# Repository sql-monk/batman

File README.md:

# batman — менеджер двох акумуляторів (LiFePO₄ 8S + свинець 24 В)

Пристрій, що заряджає два акумулятори по черзі від одного DPS5015, віддає їх на спільне навантаження через ідеальні діоди з керованими ключами, і рахує, скільки кожен акумулятор прийняв і віддав.

Основа — наявні модулі з [docs/components.md](docs/components.md). Чотири однобічні плати ЛУТ: A з ESP і двома портами I²C для ADS, B з аналоговими входами та фільтрами без I²C, C з розподілом 3,3 В, D з розподілом 5 В. Два окремі ADS1115 одержують аналог із B, живлення/I²C із A. Потрібен ще один ADS1115; C/D розподіляють готове живлення, а не замінюють стабілізатори.

| Тека | Вміст |
|---|---|
| [docs/concept.md](docs/concept.md) | задум, архітектура, вибір модулів, вимірювання й підрахунок А·год, припущення, відкриті питання |
| [docs/plan.md](docs/plan.md) | план робіт: документація, схема й плати, корпус, прошивка, сервіс; порядок і критерії готовності |
| [docs/components.md](docs/components.md) | кожен модуль і базовий компонент: характеристики, розпіновка, розміри з позначкою джерела, кількість, публічні посилання |
| [docs/README.md](docs/README.md) | зміст документації, правило «одне число — одне місце», позначення |
| [docs/connections.md](docs/connections.md) | вузли, кола з номерами, GPIO ESP32, роз'єми A–D, шкала АЦП |
| [docs/dps5015-modbus.md](docs/dps5015-modbus.md) | порт, регістри, послідовності команд, помилки DPS5015 |
| [docs/measurement.md](docs/measurement.md) | вибірка, інтегрування, автонуль, SoC, NVS |
| [docs/protocol.md](docs/protocol.md) | пристрій ↔ сервіс: пошук, JSON, REST |
| [docs/firmware.md](docs/firmware.md) | вимоги до прошивки: старт, стейт-машина, параметри |
| [docs/service.md](docs/service.md) | вимоги до сервісу: БД, агрегати, сторінки, розгортання |
| [docs/enclosure/requirements.md](docs/enclosure/requirements.md) | що вмістити, зони, зазори, тепло, друк, перелік STL |
| [docs/tests.md](docs/tests.md) | бланки перевірок і результати |
| [hardware/README.md](hardware/README.md) | єдиний проєкт KiCad 10, сім сторінок схеми, розведені A–D, PDF ЛУТ, свердління, BOM, кабелі та умови допуску прототипу |
| `firmware/` | код ESP32: вимірювання, підрахунок А·год, Modbus до DPS5015, ключі, Wi-Fi-телеметрія |
| `service/` | кросплатформений сервіс (Windows → Raspberry Pi 4): пошук пристрою, збір, зберігання, агрегати, графіки |
| `mechanical/` | модель корпусу, STL, звіти придатності до друку |

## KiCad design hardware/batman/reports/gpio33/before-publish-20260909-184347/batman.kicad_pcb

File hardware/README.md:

# BATMAN: чотири модульні PCB

**CAD-прототип, не перевірений на стенді.** Основний проєкт: [batman/batman.kicad_pro](batman/batman.kicad_pro), KiCad 10.0.6+. У [спільній PCB](batman/batman.kicad_pcb) чотири замкнені контури: це чотири фізичні плати, не одна плата з міддю між ними. Схема має кореневий і шість функціональних аркушів.

## Склад

Актуальна ревізія трасування 2026-09-09: **223 сегменти (A: 85, B: 77, C: 28, D: 33), тільки напрямки 0/45/90°**. Попередня версія зі 165 сегментами довільного напрямку замінена. Компоненти, їхні кути, контакти та чотири перемички залишені на місцях; глобальний мінімум кількості перемичок не доведений. GND з'єднує заливка. Вільні кінці трас точно збігаються з центрами контактів, інші стики мають спільні центральні лінії; сегментів коротше 1 мм немає. DRC усіх плат, паритет схеми та PDF 1:1 перевірені. Експорт відхиляє некратні 45° напрямки. Опис перенесення GPIO33 нижче стосується попереднього етапу розміщення.

| PCB | Функція | Розмір, мм | Локальні перемички | Отвори |
|---|---|---|---|---|
| A | ESP32 DevKitC, два порти ADS I²C, OLED, UART DPS, SPI, кнопка, 1-Wire, драйвери реле | 78 × 78 | WA1–WA4 | 86 |
| B | Шість аналогових входів, дільники, RC-фільтри; аналогові виходи до окремих ADS | 86 × 68 | немає | 39 |
| C | Розподіл 3,3 В і кероване живлення mACS через Q3 | 43 × 33 | немає | 18 |
| D | Розподіл 5 В, діодне «АБО» B1/B2 перед зовнішнім LM2596, зірка живлення реле | 63 × 40 | немає | 32 |

Чотири перемички WA1–WA4 на A паяються до наявних контактів; B/C/D без перемичок. WA1 (+3V3) закінчується на SMD-паді R16.2, WA4 (SCL) на R17.1: ізолювати та механічно розвантажити дроти. WA2 з'єднує кнопку J11.2 з J1.7; WA3 — SCL J20.3 з J10.2. Жодна локальна перемичка не підключається до J22. Разом 175 отворів, включно з 16 монтажними M3 Ø3,4 мм. ADS1115 J2/J13 — два зовнішні модулі, посадок під них на A–D немає.

Ревізія GPIO33 2026-09-09: 352 сегменти, усі довжиною не менше 1 мм. **SENS_PWR перенесений на J1.8 / GPIO33; J1.12 / GPIO14 тепер NC.** J22 піднятий і повернутий вертикально; усі три його контакти (+3V3, GND, SENS_PWR) з'єднані з ESP міддю без локальних перемичок. Це перевірено на копії PCB без моделей дротів. Для проходу живлення пересунутий роз'єм кнопки J11. Кабель CB2 до окремої плати C залишається потрібним. У прошивці задати SENS_PWR=33, HIGH/Hi-Z=OFF, LOW=ON; старе призначення GPIO14 непридатне. Загальна площа плат зменшена приблизно на 6%. Збережені ручні позиції J6/J7/J26/R13/R18; попередні зміни J20/J21/R16/R17, C3/C4 та роз'ємів D залишені. Старі монтажні таблиці й перемички не використовувати.

Силові 10 А батарей і навантаження не проходять через ці PCB. Зовнішні модулі, запобіжники й панельні клеми залишаються у схемі. C1/C2 навісно на зовнішній шині LOAD+/GND; D3 DNP. Нова PCB B є **аналоговою**, не колишньою платою буфера.

## Міжплатні Кабелі

Порядок у таблиці: від контакту 1 до N. Кабелі однойменні, 1→1; **не перевертати за фізичним напрямком гребінки**. Звіряти номери на монтажних PDF.

| Кабель | Звідки → куди | Контакти 1…N |
|---|---|---|
| CB2 | A.J22 → C.J23 | +3V3, GND, SENS_PWR |
| CB3 | C.J24 → B.J25 | GND, +3V3_SENS |
| CB4 | D.J27 → A.J26 | +5V, GND |
| CB5 | A.J28 → D.J29 | RELAY_IN1, RELAY_IN2, GND |
| CB6 | D.X6 → B.X8 | B1, B2, GND; напруга батарей до дільників, не рівні 3,3 В |

Між A–D п'ять кабелів, 13 жил. **CB1 вилучений; J21 тепер на A. Старі кабелі J20/J21 і J24/J25 несумісні з цією ревізією.** [interboard-cables.csv](batman/output/interboard-cables.csv) містить кожну жилу CB2–CB6. `WC*` на спільній PCB моделюють зовнішні дроти, не мідь. Лінії Dwgs.User показують відповідність кінців, не маршрут і довжину джгута.

## Підключення Окремих ADS

| Роз'єм PCB | Контакти PCB 1…N | Зовнішній модуль і контакти |
|---|---|---|
| A.J20 | +3V3, GND, SCL, SDA | J2 (0x48): VDD, GND, SCL, SDA |
| A.J21 | +3V3, GND, SCL, SDA | J13 (0x49): VDD, GND, SCL, SDA |
| B.J32 | I_B1, I_B2, U_B1, U_B2, GND | J2: A0, A1, A2, A3, GND |
| B.J33 | I_LOAD, U_LOAD, GND | J13: A0, A1, GND |

Це ще чотири кабелі, 16 жил, не включені в CB2–CB6. Точні контакти — [cable-map.csv](batman/output/cable-map.csv). На кожному ADS обидві землі кабелів з'єднати в локальній точці GND із надійною ізоляцією та розвантаженням дротів; один контакт модуля не означає два незалежні гнізда.

J20/J21 — два роз'єми **однієї** шини GPIO22=SCL/GPIO21=SDA. Є одна пара R16/R17 по 4,7 кОм до 3V3 на A; не додавати ще одну пару для другого порту. C6/C10 — локальні 100 нФ VDD–GND біля відповідного зовнішнього ADS, не на B: перевірити наявність на модулі, за відсутності встановити. Перемички ADDR та невикористані входи — [ads-configuration.csv](batman/output/ads-configuration.csv).

I²C: початково 100 кГц, короткий внутрішній кабель до 20 см, подалі від силових дротів. Перевірити фронти осцилографом і сумарні підтяжки на A, ADS-модулях та OLED: врахувати паралельний опір і допустимий струм LOW. Це не інтерфейс для довгого зовнішнього кабелю. CB6 вести окремо від I²C; дроти B1/B2 мають бути захищені від КЗ біля джерела.

## Аналогова Плата B І Канали

На B немає ADS, SDA/SCL і неперемиканої шини +3V3. Потрібні **два окремі модулі ADS1115**, один додатковий до початкового комплекту. Їхні позначення J2/J13 збережені у схемі, але мають власника EXTERNAL. Перевірити маркування `VDD GND SCL SDA ADDR ALRT A0 A1 A2 A3`. Локально на J2 ADDR з'єднати з GND, на J13 з VDD; спочатку розімкнути заводську перемичку ADDR→GND другого модуля, інакше буде КЗ. На J13 локально заземлити A2/A3, обидва ALRT залишити NC.

| АЦП | Адреса | A0 | A1 | A2 | A3 |
|---|---|---|---|---|---|
| J2 | 0x48 | I_B1 | I_B2 | U_B1 | U_B2 |
| J13 | 0x49 | I_LOAD | U_LOAD | GND | GND |

Обидва PGA ±4,096 В, 475 SPS; це діапазон перетворення, **не дозвіл перевищувати живлення на вході**. Дільники: U_B1/U_B2 100k/10k, U_LOAD 100k/4,7k. Струми через RC 1k/1u; напруги через дільники й 100n. GPIO34/39 ESP тепер NC, аналогових кабелів до A немає. ALRT не підключені, готовність опитувати через I²C.

ADS розмістити біля B; аналогові кабелі початково до 10 см, окремо від силових і цифрових джгутів. Перевірити шум та зміщення при передачі Wi-Fi й роботі реле. Усі підключення робити з вимкненим живленням: напруга на B1/B2/LOAD може підживлювати знеструмлений ADS через входи. Живі аналогові входи без живлення ADC не допускаються; схема не містить окремого захисту від такого режиму.

mACS мають лише VCC/GND/VOUT, без FAULT. J3/J4: VOUT, GND, VCC; J5: VCC, VOUT, GND. Збережене припущення ACS711EX 3,3 В / 90 мВ/А. Позначення власника `VSS` неоднозначне: **не подавати плюс без перевірки моделі та маркування**. Датчик на 5 В не є прямою заміною.

## Живлення

**C і D є розподільними платами, не новими стабілізаторами.**

- D.X1: B1, B2, GND. P28 від зовнішньої мінус-шини до D.X1.3. VD1/VD2 формують VIN_DC на D.X2.1 для входу наявного LM2596; X2.2 GND. Його вихід, заздалегідь виставлений на 5,0 В, підключається до D.X3.1/2.
- D.J27 живить VIN DevKitC на A через CB4. D.J31: резервний вихід 5V/GND, штатно без навантаження. 5 В потрібні DevKitC і реле.
- D.J8: IN1, GND, IN2, VCC, JD-VCC. Перемичку VCC–JD-VCC на реле зняти. NT1 біля X3 є мідною зіркою; гілки опто та котушок не об'єднувати біля J8.
- 3,3 В утворює стабілізатор DevKitC. A.J20/J21 живлять окремі ADS, A.J22 передає 3V3 на C.J23. C.J24 живить тільки датчики через B; Q3 комутує +3V3_SENS. SENS_PWR LOW=ON, HIGH/Hi-Z=OFF. C.J30: резервний 3V3/GND, штатно без навантаження.
- **Не підключати зовнішнє джерело до A.J20/J21 або C.J30:** це виходи 3V3 DevKitC. C.J24 також не є входом живлення. USB одночасно із зовнішнім VIN дозволений лише після перевірки конкретного DevKitC на зворотне підживлення.

Орієнтовна початкова межа зовнішнього навантаження 3,3 В: до 100 мА сумарно на ADS, mACS, OLED, підтяжки й периферію, **лише якщо конкретний DevKitC має такий запас після власного споживання**. Це не паспортний рейтинг плати. Піки Wi-Fi, котушки, нагрів LDO, падіння на Q3 й кабелях перевірити на стенді. Резервні виходи не створюють додаткової потужності. За браку запасу потрібна інша ревізія з окремим стабілізатором 3,3 В, не паралельне підключення джерел.

GND спільний. Через CB2–CB6, цифрові й аналогові кабелі ADS та UART є кілька шляхів повернення струму: модульність **не забезпечує гальванічної розв'язки чи відсутності петель землі**. Силові повернення вести окремо, перевірити топологію на стенді.

## Виготовлення

ЛУТ, тільки **B.Cu**: сигнали ≥0,8 мм; GND і живлення 3,3/5 В ≥1,0 мм; B1/B2/LOAD+/VIN_DC ≥1,2 мм. Зазор за участю доріжки ≥0,65 мм, між готовими падами ≥0,5 мм; від батарейних мереж B1/B2/LOAD+/VIN_DC до іншої міді ≥1,0 мм, включно із заливкою. Відступ від краю ≥0,5 мм. Це технологічний запас для низьковольтного батарейного пристрою, не сертифікація ізоляції та не дозвіл підвищувати робочу напругу або струм. Силові 10 А залишаються поза PCB.

Без via, mask/paste. THT-пади номінально мають F.Cu у KiCad, але цей шар не виготовляється. Резистори лише 1206; C3–C5, C7–C9, C11–C13 мають альтернативні THT/1206-пади, ставити **один** корпус на позицію. C1/C2 зовнішні на шині, C6/C10 біля зовнішніх ADS.

| Плата | Мідь, дзеркало 1:1 | Монтаж |
|---|---|---|
| A | [A/copper-mirrored.pdf](batman/output/A/copper-mirrored.pdf) | [A/assembly.pdf](batman/output/A/assembly.pdf) |
| B | [B/copper-mirrored.pdf](batman/output/B/copper-mirrored.pdf) | [B/assembly.pdf](batman/output/B/assembly.pdf) |
| C | [C/copper-mirrored.pdf](batman/output/C/copper-mirrored.pdf) | [C/assembly.pdf](batman/output/C/assembly.pdf) |
| D | [D/copper-mirrored.pdf](batman/output/D/copper-mirrored.pdf) | [D/assembly.pdf](batman/output/D/assembly.pdf) |

У кожній теці A–D є недзеркальна мідь, wiring.pdf, Excellon/карта свердління й Gerber. Спільні PDF у output показують усі чотири плати, не стару 100×80 PCB. Друк Actual size / 100%, без Fit; перевірити лінійкою контур і крок 2,54 мм.

[pinout.csv](batman/output/pinout.csv): контакти від лівого верхнього кута своєї PCB. [drill-list.csv](batman/output/drill-list.csv) і [drill-summary.csv](batman/output/drill-summary.csv): отвори за платами. [jumpers.csv](batman/output/jumpers.csv): WA1–WA4 на A. [cable-map.csv](batman/output/cable-map.csv): кабелі зовнішніх модулів, включно з ADS. [bom.csv](batman/output/bom.csv): J1 — DevKitC із гніздами, J2/J13 — окремі ADS, не дублікати модулів.

## Перевірки Та Обмеження

ERC, DRC/паритет спільної PCB, DRC кожної локальної плати та PDF 1:1: [validation.json](batman/reports/validation.json), [pdf-validation.json](batman/reports/pdf-validation.json). Експорт перевіряє відсутність міжплатної міді, сегментів коротше 1 мм та правильні контакти кабелів ADS. Для роботи потрібні чотири перемички A, п'ять кабелів CB2–CB6, чотири кабелі до ADS і їхні локальні з'єднання ADDR/A2/A3/GND. DRC не перевіряє фактичний зовнішній монтаж.

До виготовлення звірити посадки DevKitC (38 пінів, міжряддя 25,4 мм), клемників 5,00 мм, BC547/BC557 C-B-E та осьових 1N5819 K-A. MCU: USB унизу, антена зверху; keepout на A не замінює перевірки реального модуля. Зовнішні ADS закріпити на ізольованих тримачах біля B, не залишати на дротах. **Корпуси та висоти не обміряні; DRC не перевіряє їхню посадку.** Джгути не прокладати над антеною.

До підключення батарей закрити попередні питання безпеки: реле 10 А проти старої вимоги прошивки 12 А; відсутність апаратного взаємоблокування K1/K2; неможливість гарантувати безструмову комутацію при всіх відмовах DPS; ground-loop через UART. D3 DNP: напис 33 В не гарантує обмеження до 35 В. Не перевищувати 10 А на наявному реле. FAULT від mACS немає. Перший запуск з обмеженням струму, без батарей і силового навантаження. Стендові випробування не виконані.

## Відтворення

Наведений нижче старий процес **не відтворює актуальні 223 сегменти**. Поточний результат збережений у головній PCB та reports/routing45/staged. [octilinear.py](octilinear.py) обмежує маршрути напрямками 0/45/90°; [clean_paths.py](clean_paths.py) без цього обмеження дозволяє довільні кути й не відтворює поточну ревізію. Інструменти в reports/routing45 використовують історичні знімки, а не нові ручні правки. Локальні плати мають світові координати основної збірки: старий `modular.py --merge` повторно змістить їх. Для актуального комплекту не запускати старі `--finish-copper`, `polish.py` або `--merge`; перевірка та експорт головної PCB через `export.py` підтримуються.

[circuit.py](circuit.py): з'єднання й власники деталей; [connector_pinout.json](connector_pinout.json): зовнішні роз'єми; [modular-layout.json](modular-layout.json): геометрія; [modular.py](modular.py): плати й кабелі. Старі floorplan.json / placement.py / placement.json не керують цією ревізією. Прямі одноплатні входи pcb.py і freeroute.py вимкнені.

```powershell
$python = "$env:LOCALAPPDATA\Programs\KiCad\10.0\bin\python.exe"
& $python hardware/circuit.py
& $python hardware/modular.py --route --finish-copper --wire
foreach ($board in @('A', 'B', 'C', 'D')) {
	& $python hardware/polish.py "hardware/batman/reports/$board/candidate.kicad_pcb"
	if ($LASTEXITCODE -ne 0) { throw "PCB $board needs local correction" }
}
& $python hardware/modular.py --merge
& "$env:LOCALAPPDATA\Programs\KiCad\10.0\bin\kicad-cli.exe" pcb drc --refill-zones --save-board --exit-code-violations hardware/batman/batman.kicad_pcb
& $python hardware/export.py
python hardware/review_pdf.py
```

Потрібні pcbnew/numpy/sexpdata у Python KiCad, Java 25 і Freerouting 2.4.1 (`FREEROUTING_JAVA`, `FREEROUTING_JAR`, або перевірені файли в TEMP); PyMuPDF потрібний лише останній перевірці. Трасування локальне, API/аналітика вимкнені. `--board A` (або B/C/D) обмежує трасування однією платою; `--merge` збирає всі чотири. Не використовувати старі SES після зміни контактів чи геометрії.

Генератори **перезаписують** CAD. Не запускати поверх ручних правок без перенесення їх у модель. Технічні знімки й настройки DRC у reports/A–D, відкривати для роботи основний batman.kicad_pro. [batman.kicad_dru](batman/batman.kicad_dru) переносити разом із проєктом. Після зовнішньої перебудови не зберігати старий відкритий у KiCad вміст поверх нового.

[polish.py](polish.py) є історичним інструментом видалення та злиття коротких сегментів; подовження окремих шматків прибране. Чистий DRC сам по собі не гарантує акуратних стиків центральних ліній. [refine.py](refine.py) зберігає історичний експеримент у reports/refinement, використовує зафіксований saved-input і не є входом для імпорту майбутніх ручних правок.

[gpio33.py](gpio33.py) зберігає кандидат перенесення GPIO33 у reports/gpio33. `--check-j22` вилучає моделі перемичок тільки з тестової копії та перевіряє мідну зв'язність J22 з J1 по всіх трьох мережах. Очікувані обриви інших мереж у copper-only-drc.json не є DRC виробничої PCB. Скрипт використовує свій зафіксований saved-input; для майбутніх ручних правок цей знімок не є актуальним джерелом.

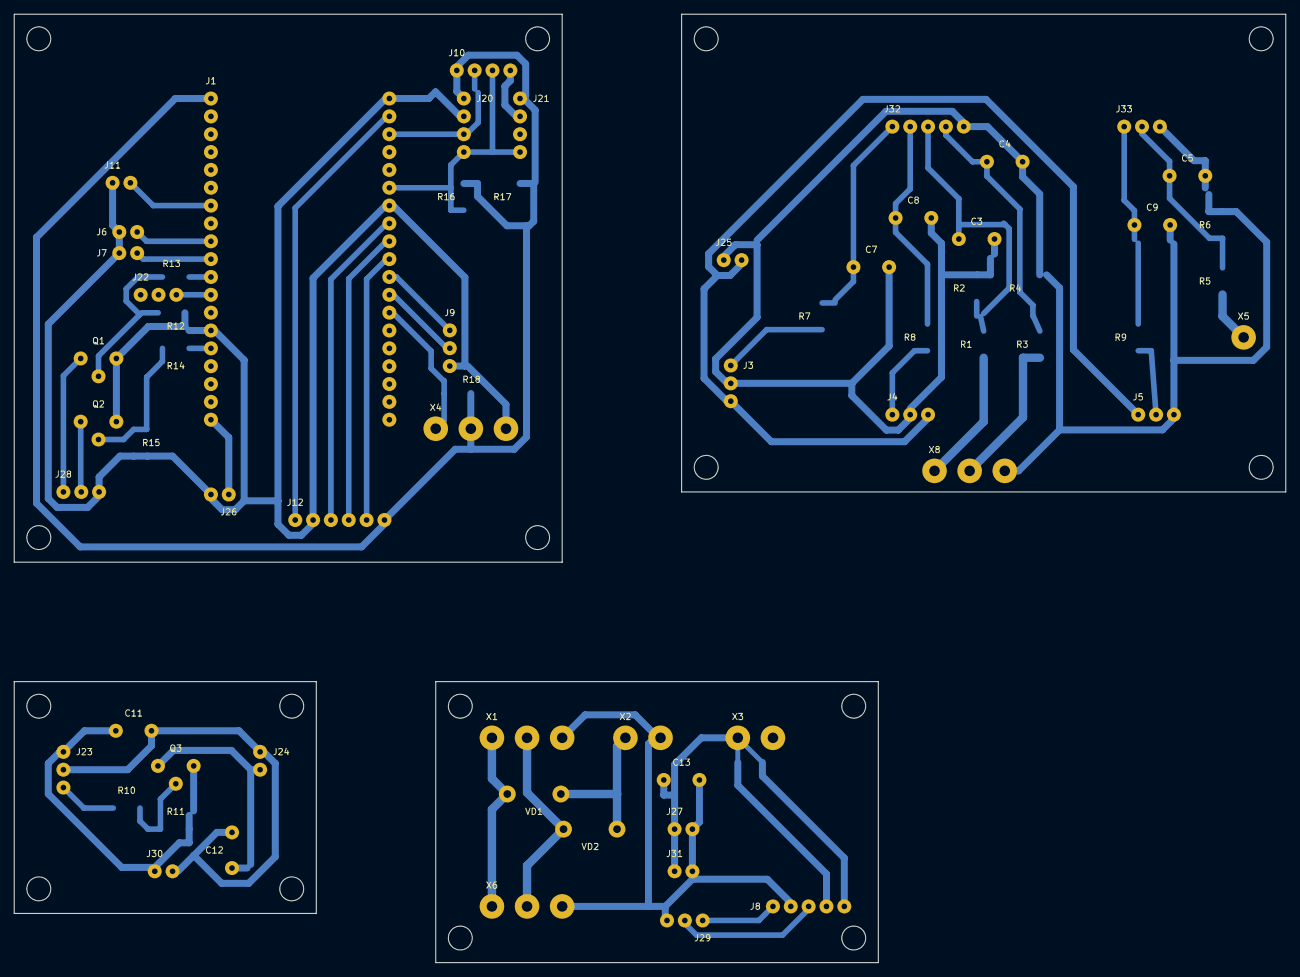
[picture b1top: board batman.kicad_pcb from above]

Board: 2 copper layers, 181.0 x 135.0 mm, 99 parts (0 on the bottom side), 39 nets.

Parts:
C3: 100n_50V; LUT_C3
C4: 100n_50V; LUT_C4
C5: 100n_50V; LUT_C5
C7: 1u_16V; LUT_C7
C8: 1u_16V; LUT_C8
C9: 1u_16V; LUT_C9
C11: 100n_16V; LUT_C11
C12: 100n_16V; LUT_C12
C13: 100n_16V; LUT_C13
HA1, HA2, HA3, HA4: M3_NPTH_3.4; Mount_M3
HB1, HB2, HB3, HB4: M3_NPTH_3.4; Mount_M3
HC1, HC2, HC3, HC4: M3_NPTH_3.4; Mount_M3
HD1, HD2, HD3, HD4: M3_NPTH_3.4; Mount_M3
J1: DevKitC_38_socket_mMCU; LUT_J1
J3: ACS1_3WIRE; LUT_J3
J4: ACS2_3WIRE; LUT_J4
J5: ACS3_3WIRE; LUT_J5
J6: SW1_GND_ON; LUT_J6
J7: SW2_GND_ON; LUT_J7
J8: RELAY; LUT_J8
J9: DPS_UART; LUT_J9
J10: OLED_I2C; LUT_J10
J11: BUTTON; LUT_J11
J12: SPI; LUT_J12
J20: LINK_+3V3_GND_SCL_SDA; LUT_J20
J21: LINK_+3V3_GND_SCL_SDA; LUT_J21
J22: LINK_+3V3_GND_SENS_PWR; LUT_J22
J23: LINK_+3V3_GND_SENS_PWR; LUT_J23
J24: LINK_GND_+3V3_SENS; LUT_J24
J25: LINK_GND_+3V3_SENS; LUT_J25
J26: LINK_+5V_GND; LUT_J26
J27: LINK_+5V_GND; LUT_J27
J28: LINK_RELAY_IN1_RELAY_IN2_GND; LUT_J28
J29: LINK_RELAY_IN1_RELAY_IN2_GND; LUT_J29
J30: LINK_+3V3_GND; LUT_J30
J31: LINK_+5V_GND; LUT_J31
J32: LINK_I_B1_I_B2_U_B1_U_B2_GND; LUT_J32
J33: LINK_I_LOAD_U_LOAD_GND; LUT_J33
NT1: COPPER_STAR_AT_X3; LUT_NT1
Q1: BC547_CBE; LUT_Q1
Q2: BC547_CBE; LUT_Q2
Q3: BC557_CBE; LUT_Q3
R1: 100k_1%; LUT_R1
R2: 10k_1%; LUT_R2
R3: 100k_1%; LUT_R3
R4: 10k_1%; LUT_R4
R5: 100k_1%; LUT_R5
R6: 4.7k_1%; LUT_R6
R7: 1k; LUT_R7
R8: 1k; LUT_R8
R9: 1k; LUT_R9
R10: 4.7k; LUT_R10
R11: 10k; LUT_R11
R12: 1k; LUT_R12
R13: 10k; LUT_R13
R14: 1k; LUT_R14
R15: 10k; LUT_R15
R16: 4.7k; LUT_R16
R17: 4.7k; LUT_R17
R18: 4.7k; LUT_R18
VD1: 1N5819; LUT_VD1
VD2: 1N5819; LUT_VD2
WA1: INSULATED_WIRE; LUT_WA1
WA2: INSULATED_WIRE; LUT_WA2
WA3: INSULATED_WIRE; LUT_WA3
WA4: INSULATED_WIRE; LUT_WA4
WA5: INSULATED_WIRE; LUT_WA5
WC2_1: EXTERNAL_CABLE_NOT_PCB; LUT_WC2_1
WC2_2: EXTERNAL_CABLE_NOT_PCB; LUT_WC2_2
WC2_3: EXTERNAL_CABLE_NOT_PCB; LUT_WC2_3
WC3_1: EXTERNAL_CABLE_NOT_PCB; LUT_WC3_1
WC3_2: EXTERNAL_CABLE_NOT_PCB; LUT_WC3_2
WC4_1: EXTERNAL_CABLE_NOT_PCB; LUT_WC4_1
WC4_2: EXTERNAL_CABLE_NOT_PCB; LUT_WC4_2
WC5_1: EXTERNAL_CABLE_NOT_PCB; LUT_WC5_1
WC5_2: EXTERNAL_CABLE_NOT_PCB; LUT_WC5_2
WC5_3: EXTERNAL_CABLE_NOT_PCB; LUT_WC5_3
WC6_1: EXTERNAL_CABLE_NOT_PCB; LUT_WC6_1
WC6_2: EXTERNAL_CABLE_NOT_PCB; LUT_WC6_2
WC6_3: EXTERNAL_CABLE_NOT_PCB; LUT_WC6_3
X1: B1_B2_GND; LUT_X1
X2: VIN_DC_GND; LUT_X2
X3: 5V_GND; LUT_X3
X4: DS18B20; LUT_X4
X5: U_LOAD_SENSE; LUT_X5
X6: BAT_SENSE_TO_B; LUT_X6
X8: BAT_SENSE_FROM_D; LUT_X8

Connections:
+3V3: C11.1, J1.1, J10.1, J12.6, J20.1, J21.1, J22.1, J23.1, J30.1, Q3.3, R11.2, R16.2, R17.2, R18.2, WA1.1, WC2_1.1, X4.2
+3V3_SENS: C12.1, J3.3, J4.3, J5.1, J24.2, J25.2, Q3.1, WC3_2.1
+5V: C13.1, J1.19, J26.1, J27.1, J31.1, NT1.1, WC4_1.1, X3.1
+5V_RELAY_COIL: J8.5, NT1.3
+5V_RELAY_VCC: J8.4, NT1.2
B1: R1.1, VD1.2, WC6_1.1, X1.1, X6.1, X8.1
B2: R3.1, VD2.2, WC6_2.1, X1.2, X6.2, X8.2
BASE1: Q1.2, R12.2, R13.1
BASE2: Q2.2, R14.2, R15.1
BASE3: Q3.2, R10.2, R11.1
BTN: J1.7, J11.2
CS: J1.29, J12.5
DPS_RX: J1.31, J9.2
DPS_TX: J1.30, J9.1
GND: C3.2, C4.2, C5.2, C7.2, C8.2, C9.2, C11.2, C12.2, C13.2, J1.14, J1.20, J1.26, J3.2, J4.2, J5.3, J6.1, J7.1, J8.2, J9.3, J10.4, J11.1, J12.2, J20.2, J21.2, J22.2, J23.2, J24.1, J25.1, J26.2, J27.2, J28.3, J29.3, J30.2, J31.2, J32.5, J33.3, Q1.3, Q2.3, R2.2, R4.2, R6.2, R13.2, R15.2, WA2.1, WA3.1, WC2_2.1, WC3_1.1, WC4_2.1, WC5_3.1, WC6_3.1, X1.3, X2.2, X3.2, X4.3, X6.3, X8.3
I_B1: C7.1, J32.1, R7.2
I_B2: C8.1, J32.2, R8.2
I_LOAD: C9.1, J33.1, R9.2
I_RAW1: J3.1, R7.1
I_RAW2: J4.1, R8.1
I_RAW3: J5.2, R9.1
K1: J1.11, R12.1
K2: J1.15, R14.1
LOAD+: R5.1, X5.1
MISO: J1.27, J12.3
MOSI: J1.21, J12.1
OW: J1.32, R18.1, X4.1
RELAY_IN1: J8.1, J28.1, J29.1, Q1.1, WC5_1.1
RELAY_IN2: J8.3, J28.2, J29.2, Q2.1, WC5_2.1
SCK: J1.28, J12.4
SCL: J1.22, J10.2, J20.3, J21.3, R17.1, WA4.1, WA5.1
SDA: J1.25, J10.3, J20.4, J21.4, R16.1
SENS_PWR: J1.12, J22.3, J23.3, R10.1, WC2_3.1
SW1_ON: J1.9, J6.2
SW2_ON: J1.10, J7.2
U_B1: C3.1, J32.3, R1.2, R2.1
U_B2: C4.1, J32.4, R3.2, R4.1
U_LOAD: C5.1, J33.2, R5.2, R6.1
VIN_DC: VD1.1, VD2.1, X2.1

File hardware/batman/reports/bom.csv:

Reference,Documentation_alias,Value,Quantity,Location,Populate
J1,,DevKitC_38_socket_mMCU,1,A,yes
J2,,ADS1115_socket_mADC,1,A,yes
J3,,ACS1_3WIRE,1,A,yes
J4,,ACS2_3WIRE,1,A,yes
J5,,ACS3_3WIRE,1,A,yes
J6,,SW1_GND_ON,1,A,yes
J7,,SW2_GND_ON,1,A,yes
J8,,RELAY,1,A,yes
J9,,DPS_UART,1,A,yes
J10,,OLED_I2C,1,A,yes
J11,,BUTTON,1,A,yes
J12,,SPI,1,A,yes
X1,,B1_B2_GND,1,A,yes
X2,,VIN_DC_GND,1,A,yes
X3,,5V_GND,1,A,yes
X4,,DS18B20,1,A,yes
X5,,U_LOAD_SENSE,1,A,yes
NT1,,COPPER_STAR_AT_X3,1,A,copper only
VD1,,1N5819,1,A,yes
VD2,,1N5819,1,A,yes
R1,,100k_1%,1,A,yes
R2,,10k_1%,1,A,yes
C3,,100n_50V,1,A,yes
R3,,100k_1%,1,A,yes
R4,,10k_1%,1,A,yes
C4,,100n_50V,1,A,yes
R5,,100k_1%,1,A,yes
R6,,4.7k_1%,1,A,yes
C5,,100n_50V,1,A,yes
R7,,1k,1,A,yes
C7,,1u_16V,1,A,yes
R8,,1k,1,A,yes
C8,,1u_16V,1,A,yes
R9,,1k,1,A,yes
C9,,1u_16V,1,A,yes
C6,,100n_16V,1,A,yes
R10,,4.7k,1,A,yes
R11,,10k,1,A,yes
Q3,,BC557_CBE,1,A,yes
R12,,1k,1,A,yes
R13,,10k,1,A,yes
Q1,,BC547_CBE,1,A,yes
R14,,1k,1,A,yes
R15,,10k,1,A,yes
Q2,,BC547_CBE,1,A,yes
R16,,4.7k,1,A,yes
R17,,4.7k,1,A,yes
R18,,4.7k,1,A,yes
XLP1,XLP,LOAD_P06_P12_P13,1,external,yes
XGND1,XGND,GND_P24_P25_P26_P27_P28,1,external,yes
C1,,100u_50V_ALUMINIUM,1,external,yes
C2,,100n_50V,1,external,yes
D3,,1.5KE33A_DNP,1,external,DNP
XB1,,BAT1_PANEL,1,external,yes
F1,,ATO_15A,1,external,yes
mACS1,,ACS711EX_15.5A,1,external,yes
mSW1,,Pololu_2815_HP,1,external,yes
mDIO1,,XL74610,1,external,yes
XB2,,BAT2_PANEL,1,external,yes
F2,,ATO_15A,1,external,yes
mACS2,,ACS711EX_15.5A,1,external,yes
mSW2,,Pololu_2815_HP,1,external,yes
mDIO2,,XL74610,1,external,yes
mACS3,,ACS711EX_15.5A,1,external,yes
Fout1,Fout,ATO_15A,1,external,yes
XLOAD1,XLOAD,LOAD_PANEL,1,external,yes
XPSU1,XPSU,PSU_33V_10A_PANEL,1,external,yes
mDPS1,mDPS,DPS5015_9600_8N1_ADDR1,1,external,yes
Fchg1,Fchg,ATO_15A,1,external,yes
mDIO3,,XL74610,1,external,yes
mREL2,,FL_3FF_5V_10A_REMOVE_JUMPER,1,external,yes
mDC5,,LM2596_SET_5.0V_FIRST,1,external,yes
mOLED1,mOLED,SSD1306_0x3C,1,external,yes
T1,,DS18B20_PROBE,1,external,yes
T2,,DS18B20_PROBE,1,external,yes
SW1,,PANEL_BUTTON_NO,1,external,yes

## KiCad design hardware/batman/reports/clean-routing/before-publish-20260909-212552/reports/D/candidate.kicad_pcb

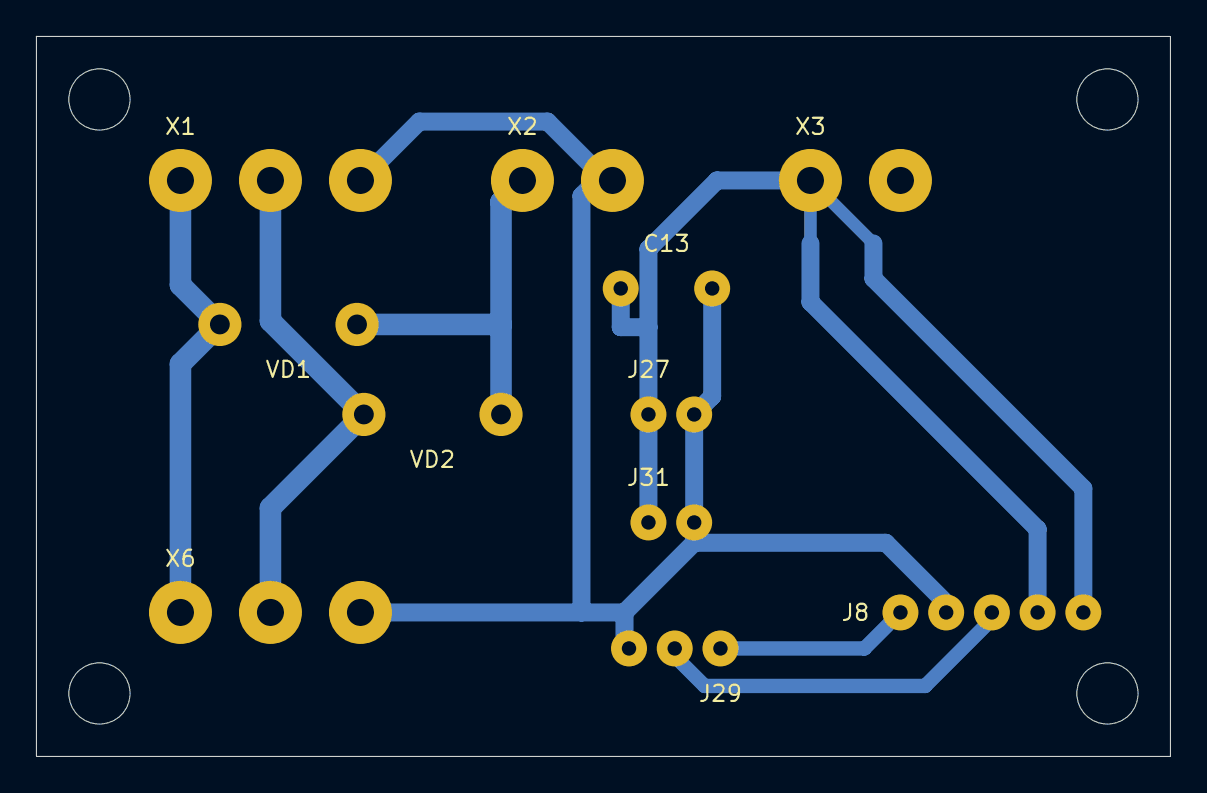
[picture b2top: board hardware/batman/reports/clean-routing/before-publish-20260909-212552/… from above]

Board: 2 copper layers, 63.0 x 40.0 mm, 16 parts (0 on the bottom side), 9 nets.

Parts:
C13: 100n_16V; LUT_C13
HD1, HD2, HD3, HD4: M3_NPTH_3.4; Mount_M3
J8: RELAY; LUT_J8
J27: LINK_+5V_GND; LUT_J27
J29: LINK_RELAY_IN1_RELAY_IN2_GND; LUT_J29
J31: LINK_+5V_GND; LUT_J31
NT1: COPPER_STAR_AT_X3; LUT_NT1
VD1: 1N5819; LUT_VD1
VD2: 1N5819; LUT_VD2
X1: B1_B2_GND; LUT_X1
X2: VIN_DC_GND; LUT_X2
X3: 5V_GND; LUT_X3
X6: BAT_SENSE_TO_B; LUT_X6

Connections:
+5V: C13.1, J27.1, J31.1, NT1.1, X3.1
+5V_RELAY_COIL: J8.5, NT1.3
+5V_RELAY_VCC: J8.4, NT1.2
B1: VD1.2, X1.1, X6.1
B2: VD2.2, X1.2, X6.2
GND: C13.2, J8.2, J27.2, J29.3, J31.2, X1.3, X2.2, X3.2, X6.3
RELAY_IN1: J8.1, J29.1
RELAY_IN2: J8.3, J29.2
VIN_DC: VD1.1, VD2.1, X2.1

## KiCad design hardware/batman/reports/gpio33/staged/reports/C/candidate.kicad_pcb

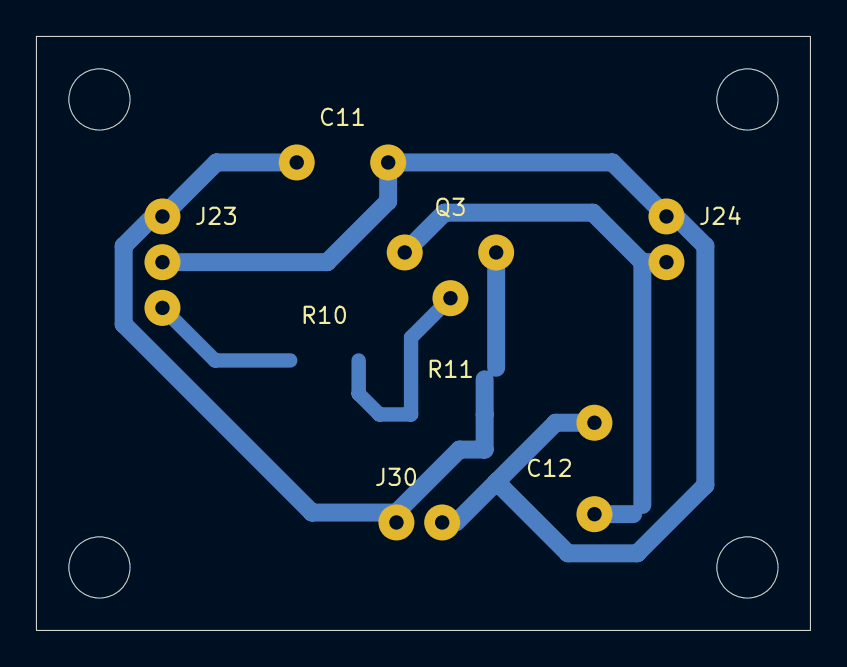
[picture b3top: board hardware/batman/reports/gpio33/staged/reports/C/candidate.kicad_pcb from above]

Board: 2 copper layers, 43.0 x 33.0 mm, 12 parts (0 on the bottom side), 5 nets.

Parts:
C11: 100n_16V; LUT_C11
C12: 100n_16V; LUT_C12
HC1, HC2, HC3, HC4: M3_NPTH_3.4; Mount_M3
J23: LINK_+3V3_GND_SENS_PWR; LUT_J23
J24: LINK_GND_+3V3_SENS; LUT_J24
J30: LINK_+3V3_GND; LUT_J30
Q3: BC557_CBE; LUT_Q3
R10: 4.7k; LUT_R10
R11: 10k; LUT_R11

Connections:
+3V3: C11.1, J23.1, J30.1, Q3.3, R11.2
+3V3_SENS: C12.1, J24.2, Q3.1
BASE3: Q3.2, R10.2, R11.1
GND: C11.2, C12.2, J23.2, J24.1, J30.2
SENS_PWR: J23.3, R10.1

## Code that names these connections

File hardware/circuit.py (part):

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    right = ["GND", "GPIO23", "GPIO22", "GPIO1", "GPIO3", "GPIO21", "GND", "GPIO19",
             "GPIO18", "GPIO5", "GPIO17", "GPIO16", "GPIO4", "GPIO0", "GPIO2",
             "GPIO15", "GPIO8", "GPIO7", "GPIO6"]
    gpio = {"3V3": "+3V3", "GND": "GND", "VIN": "+5V", "GPIO39": "I_LOAD",
            "GPIO34": "U_LOAD", "GPIO32": "BTN", "GPIO25": "SW1_ON",
            "GPIO26": "SW2_ON", "GPIO27": "K1", "GPIO33": "SENS_PWR", "GPIO13": "K2",
            "GPIO23": "MOSI", "GPIO22": "SCL", "GPIO21": "SDA", "GPIO19": "MISO",
            "GPIO18": "SCK", "GPIO5": "CS", "GPIO17": "DPS_TX", "GPIO16": "DPS_RX",
            "GPIO4": "OW"}
    pin_names = left + right
    pin_types = ["power_out" if name == "3V3" else "power_in" if name in ("GND", "VIN")
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    assert len(by_ref) == len(parts)
    pins = {name: net for _, name, net, _ in by_ref["J1"].pins}
    assert pins["GPIO39"] is None and pins["GPIO34"] is None
    assert pins["GPIO33"] == "SENS_PWR"
    assert pins["GPIO14"] is None
    assert ("8", "GPIO33", "SENS_PWR", "bidirectional") in by_ref["J1"].pins
    assert not any(net == "FAULT" for part in parts for _, _, net, _ in part.pins)
    assert all(pins[f"GPIO{number}"] is None for number in [0, 2, 6, 7, 8, 9, 10, 11, 12, 15])
    assert pins["GPIO22"] == "SCL" and pins["GPIO21"] == "SDA" and pins["GPIO23"] == "MOSI"
    assert [pin[2] for pin in by_ref["J2"].pins][-4:] == ["I_B1", "I_B2", "U_B1", "U_B2"]
    assert [pin[2] for pin in by_ref["J13"].pins][-4:] == ["I_LOAD", "U_LOAD", "GND", "GND"]
    assert by_ref["J2"].pins[4][2] == "GND" and by_ref["J13"].pins[4][2] == "+3V3"
    assert all(not by_ref[ref].board for ref in ["J2", "J13", "C6", "C10"])
    assert not any(net in ["SDA", "SCL", "+3V3"] for part in parts if part.board == "B"
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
